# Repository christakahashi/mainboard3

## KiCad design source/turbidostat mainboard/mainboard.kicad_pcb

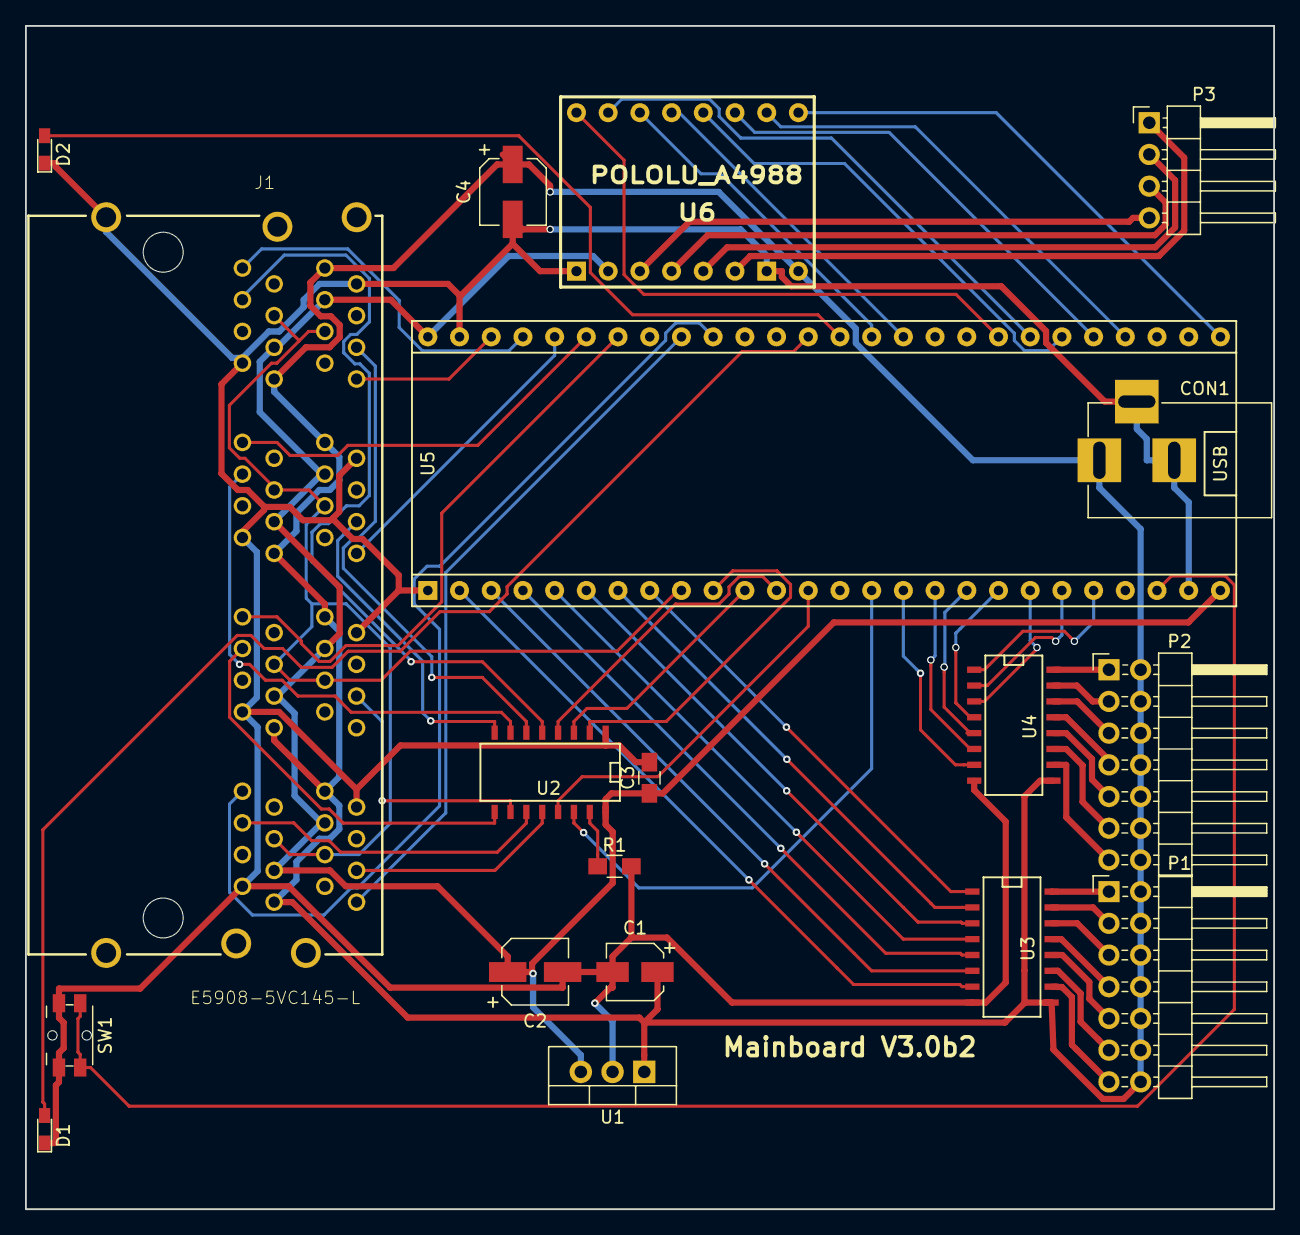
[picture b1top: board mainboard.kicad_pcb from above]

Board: 2 copper layers, 100.0 x 94.8 mm, 19 parts (0 on the bottom side), 68 nets.

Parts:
C1: 22uF; CP_Elec_4x5.3
C2, C4: 47uF; CP_Elec_5x5.3
C3: 1uF; C_0805_HandSoldering
CON1: BARREL_JACK
D1, D2: LED; LED_0603_HandSoldering
J1: E5908-5VC145-L; PULSE_E5908-5VC145-L
P1, P2: CONN_02X07; Pin_Header_Angled_2x07_Pitch2.54mm
P3: CONN_01X04; Pin_Header_Angled_1x04_Pitch2.54mm
R1: 1K21; R_0805_HandSoldering
SW1: SW_Push; Panasonic_EVQPUM_EVQPUD
U1: 5v Reg Mod; TO-220_Vertical
U2: TLC5917ID; SO-16-N
U3, U4: ULN2003A; SO-16-N
U5: CY8CKIT-059_Target; CY8KIT-059_Target
U6: POLOLU_A4988; SWDIP8_.6W

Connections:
+12V: C1.1, C4.1, CON1.1, J1.A8, J1.B8, J1.C8, J1.D8, J1.E8, J1.F8, J1.G8, J1.H8, P1.2, P1.4, P1.6, P1.8, P1.10, P1.12, P1.14, P2.2, P2.4, P2.6, P2.8, P2.10, P2.12, P2.14, U1.1, U3.9, U4.9, U6.8
/RX0: J1.H1, U5.43
/RX1: J1.G1, U5.44
/RX2: J1.F1, U5.46
/RX4: J1.D1, U5.47
/RX5: J1.C1, U5.48
/RX6: J1.B1, U5.49
/RX7: J1.A1, U5.50
/TX: J1.A4, J1.B4, J1.C4, J1.D4, J1.E4, J1.F4, J1.G4, J1.H4, U5.9
GND: C1.2, C2.2, C3.2, C4.2, CON1.2, CON1.3, D1.1, D2.1, J1.A7, J1.B7, J1.C7, J1.D7, J1.E7, J1.F7, J1.G7, J1.H7, J1.P3, R1.2, SW1.1, U1.2, U2.1, U3.8, U4.8, U5.1, U5.25, U5.51, U6.1, U6.7
unnamed: D1.2, U5.40
unnamed: D2.2, U5.39
unnamed: J1.A3, U2.6
unnamed: J1.B3, U2.5
unnamed: J1.C3, U2.8
unnamed: J1.D3, U2.7
unnamed: J1.E3, U2.10
unnamed: J1.F3, U2.9
unnamed: J1.G3, U2.12
unnamed: J1.H3, U2.11
unnamed: P1.1, U3.16
unnamed: P1.3, U3.15
unnamed: P1.5, U3.14
unnamed: P1.7, U3.13
unnamed: P1.9, U3.12
unnamed: P1.11, U3.11
unnamed: P1.13, U3.10
unnamed: P2.1, U4.16
unnamed: P2.3, U4.15
unnamed: P2.5, U4.14
unnamed: P2.7, U4.13
unnamed: P2.9, U4.12
unnamed: P2.11, U4.11
unnamed: P2.13, U4.10
unnamed: P3.1, U6.6
unnamed: P3.2, U6.5
unnamed: P3.3, U6.4
unnamed: P3.4, U6.3
unnamed: R1.1, U2.15
unnamed: SW1.2, U5.24
unnamed: U2.2, U5.10
unnamed: U2.3, U5.11
unnamed: U2.4, U5.12
unnamed: U2.13, U5.13
unnamed: U2.14, U5.15
unnamed: U3.1, U5.8
unnamed: U3.2, U5.7
unnamed: U3.3, U5.6
unnamed: U3.4, U5.5
unnamed: U3.5, U5.4
unnamed: U3.6, U5.3
unnamed: U3.7, U5.2
unnamed: U4.1, U5.22
unnamed: U4.2, U5.21
unnamed: U4.3, U5.20
unnamed: U4.4, U5.19
unnamed: U4.5, U5.18
unnamed: U4.6, U5.17
unnamed: U4.7, U5.16
unnamed: U5.27, U6.9
unnamed: U5.30, U6.10
unnamed: U5.31, U6.11
unnamed: U5.32, U6.12
unnamed: U5.33, U6.15
unnamed: U5.34, U6.16
unnamed: U5.37, U6.13
unnamed: U5.38, U6.14
VCC: C2.1, C3.1, J1.A6, J1.B6, J1.C6, J1.D6, J1.E6, J1.F6, J1.G6, J1.H6, U1.3, U2.16, U5.26, U5.52, U6.2

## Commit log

2019-10-22 working
2019-11-14 box version
